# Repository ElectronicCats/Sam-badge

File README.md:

# Badge Sam Dulces Sueños
## Reto de soldadura 

Divierte con nuestro nuevo Badge!, __“Sam dulces sueños”__ ha llegado y es increíblemente bonito y tierno. Está creado para enseñarte a soldar tu primera placa electrónica de componentes de soldado superficial SMD. ¿Aceptas el reto?.

Aunque originalmente este badge fue realizado para presentarse como taller en el evento de innovación y tecnología __“Talent Land 2020”__, no queríamos dejarte sin la experiencia de crear y aprender con nuestro aventurero amigo Sam, por lo tanto debido a la contingencia sanitaria el evento solo se realizará de manera virtual el próximo 8 y 9 de Julio en Iron Land @ Home. 

Nuestros amigos de **Wurth Electronics, Talent Land, PCBWay y Electronic Cats**, queremos regalarte uno de los 200 badge que tenemos disponibles, para que participes en este reto desde la comodidad de tu casa.

¡Nosotros ponemos la electrónica, tu solo paga el envío!. 

Lo único que debes hacer es cubrir el costo del envio hasta tu domicilio y tener en cuenta los requerimientos para participar. 
Una vez realizado el pedido, enviaremos tu badge y tendrás hasta el **3 de Julio del 2020** para subir a redes sociales tus  fotografías o videos de tu __“Sam dulces sueños”__ ensamblado y funcionando. Recuerda que deberás etiquetar a Wurth Electronics, Talend Land, PCBWay y Electronic Cats en tu post en cualquiera de nuestras redes sociales participantes. 

Redes sociales participantes:
- **"Instagram"** electroniccats/Whurth Electronics/PCBWay
- **"Twitter"** electronicats/Whurth Electronics/PCBWay
- **"Facebook"** electroniccats/Whurth Electronics/PCBWay

## Requerimientos:
- Se requieren conocimientos de nivel medio en electrónica y soldadura de componentes eléctricos para este kit, 
- Necesitas tener un programador ST LinkV2, Jlink o cualquier otro programador que soporte el protocolo SWIM.

### La Electrónica

¡Este kit tiene dos LED con diferentes patrones de luz y sorprendentes colores de PCB! 

Una vez que la placa es ensamblada, se debe programar con ST LinkV2 , Jlink o cualquier otro programador que soporte el protocolo SWIM por medio de su puerto SWD, los LEDs de la placa parpadearan y cambiará de color hasta que la batería se agote. El botón incluido en el kit te permite reiniciar el pequeño microcontrolador STM8.

Para más detalles, esquemáticos y firmware puedes consultar en nuestro repositorio de Github: https://github.com/ElectronicCats/Sam-badge

### Este kit contiene:

- 1 x Placa PCB Sam Durmiendo
- 1 x STM8S003F3P
- 4 x [LED RGB 156120M173000](https://www.mouser.mx/datasheet/2/445/156120M173000-1715570.pdf)
- 1 x Botón
- 1 x Resistencia 10K
- 1 x Capacitor 1uF
- 1 x Capacitor 0.1uF
- 1 x Soporte de batería CR2032
- NO INCLUYE BATERÍAS (batería CR2032)

## El Premio
Si eres uno de los 10 primeros participantes en subir a redes sociales tu video o fotos y nos etiquetas, te enviaremos un paquete de souvenirs de Wurth hasta las puertas de tu casa completamente gratis.

El **09 de Julio del 2020** anunciaremos durante la transmisión de Iron Land @ home a los ganadores del concurso en vivo y mostraremos su trabajo.

## Video de Ensamblado

## License

Electronic Cats invests time and resources providing this open source design, please support Electronic Cats and open-source hardware by purchasing products from Electronic Cats!

Designed by Electronic Cats.

Firmware released under an GNU AGPL v3.0 license. See the LICENSE file for more information.

Hardware released under an CERN Open Hardware Licence v1.2. See the LICENSE_HARDWARE file for more information.

Electronic Cats is a registered trademark, please do not use if you sell these PCBs.

Jun 2020

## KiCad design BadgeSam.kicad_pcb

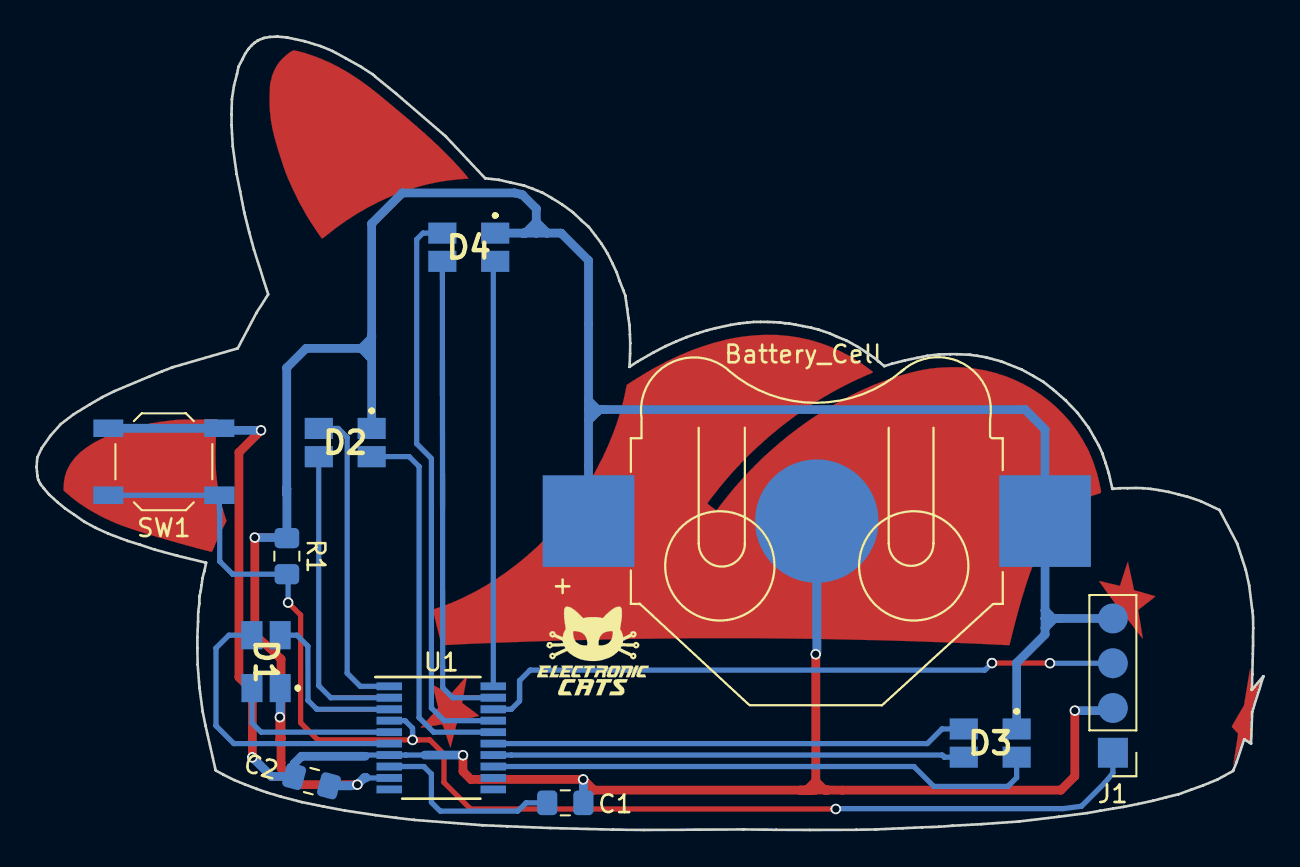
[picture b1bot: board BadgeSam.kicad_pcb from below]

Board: 2 copper layers, 69.6 x 45.0 mm, 12 parts (11 on the bottom side), 17 nets.

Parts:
BT1: Battery_Cell; 79523141
C1: 1uF; C_0805_2012Metric_Pad1.15x1.40mm_HandSolder
C2: 0.1uF; C_0805_2012Metric_Pad1.15x1.40mm_HandSolder
D1, D2, D3, D4: LED_ARGB; 156120M173000
J1: PROG; PinHeader_1x04_P2.54mm_Vertical
R1: 10K; R_0805_2012Metric_Pad1.15x1.40mm_HandSolder
Ref**: Val**; BadgeSam
SW1: RESET; SW_SPST_TL3342
U1: STM8S003F3P; TSSOP-20_4.4x6.5mm_P0.65mm

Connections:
+BATT: BT1.1, C2.1, D1.1, D2.1, D3.1, D4.1, J1.4, R1.1, U1.9
/B1: D1.4, U1.3
/B2: D3.4, U1.15
/B3: D4.4, U1.17
/B4: D2.4, U1.1
/G1: D1.3, U1.6
/G2: D3.3, U1.14
/G3: D4.3, U1.19
/G4: D2.3, U1.2
/R1: D1.2, U1.5
/R2: D3.2, U1.13
/R3: D4.2, U1.20
/R4: D2.2, U1.16
/RST: J1.1, R1.2, SW1.1, U1.4
/SWIM: J1.3, U1.18
GND: BT1.2, C1.2, C2.2, J1.2, SW1.2, U1.7
unnamed: C1.1, U1.8

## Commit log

2020-02-13 Initial pcb
2020-02-13 schematic
2020-02-13 add r g b and button
2020-02-14 battery
2020-02-14 add logo wurth
2020-02-14 add library for badge sam and battery holder
2020-02-14 add footprint LED
2020-02-15 define size
2020-02-17 Add EdgeCut and logos
2020-02-17 Routeo
2020-02-17 fix routeo
2020-02-19 change rgb and footprint led
2020-02-20 routeo and pin prog
2020-02-20 fix track batt
2020-02-20 Fix leds and traces
2020-02-21 add pcbway logo
2020-06-02 fix path
2020-06-02 update list
2020-06-04 update BOM list
2020-06-11 Add video
2020-06-11 Update link store
2020-06-12 Add Firmware
2020-06-16 Create LICENSE
